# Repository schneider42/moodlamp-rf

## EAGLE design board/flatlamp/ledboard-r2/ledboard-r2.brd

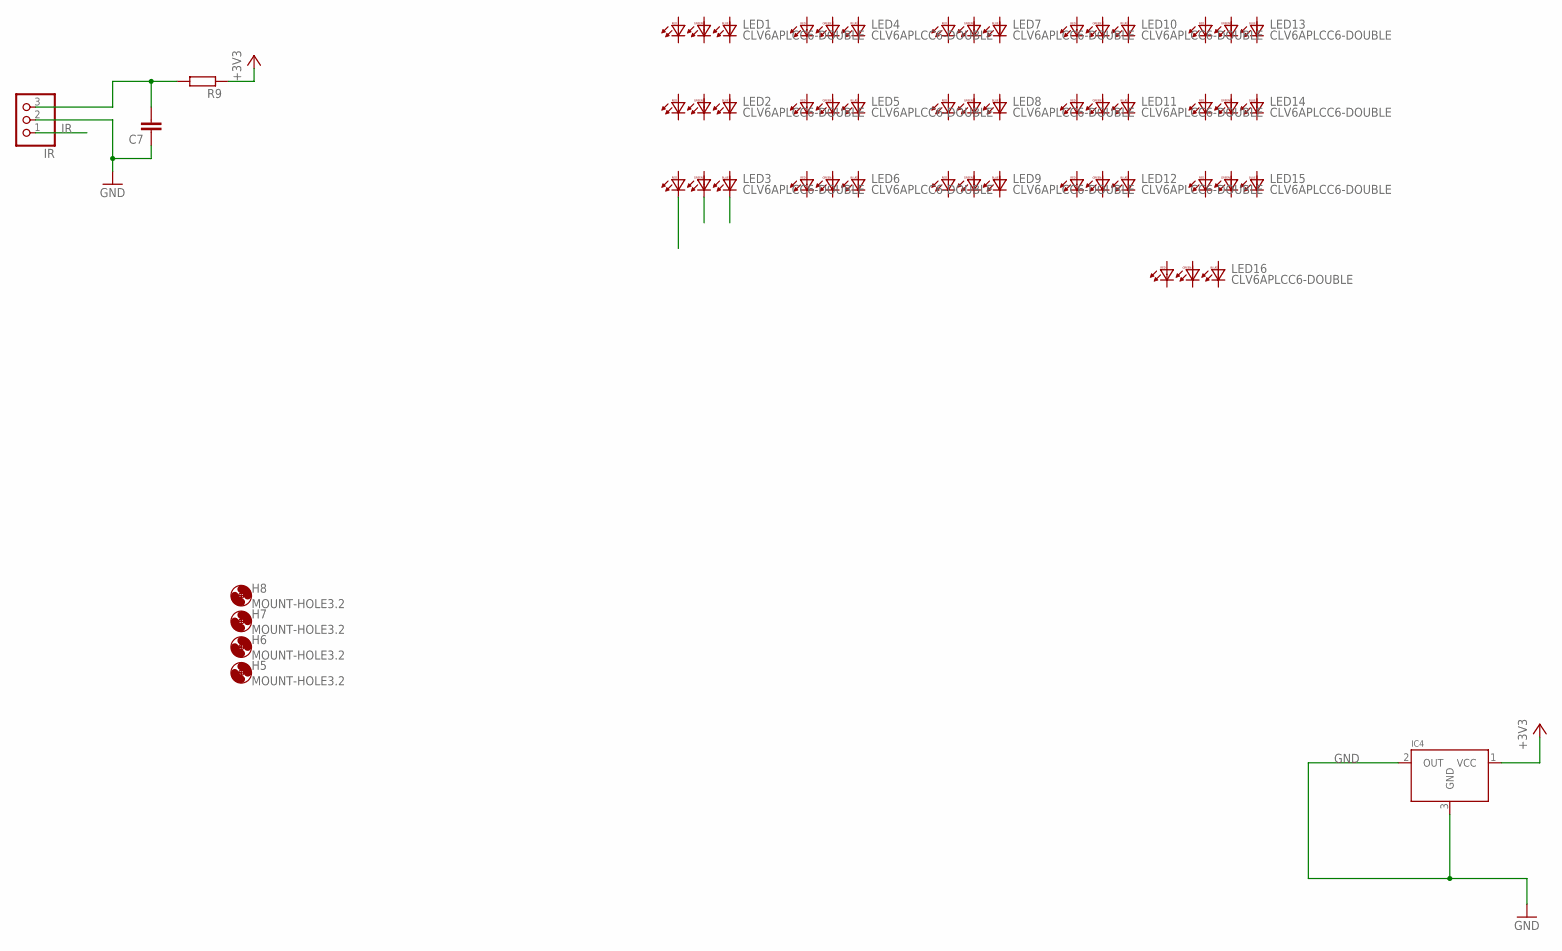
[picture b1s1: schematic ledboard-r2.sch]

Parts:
C7: C-EUC0805; C0805
H5, H6, H7, H8: MOUNT-HOLE3.2; 3,2
IC4: MCP9701T-E/TTCTREFLOW; SOT23-R
IR: PINHD-1X3; 1X03
LED1, LED2, LED3, LED4, LED5, LED6, LED7, LED8, LED9, LED10, LED11, LED12, LED13, LED14, LED15, LED16: CLV6APLCC6-DOUBLE; PLCC6-DOUBLE
R9: R-EU_R0805; R0805

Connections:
+3V3: IC4.1 (VCC), R9.1
GND: C7.1, IC4.2 (OUT), IC4.3 (GND), IR.2
IR: IR.1
unnamed: C7.2, IR.3, R9.2

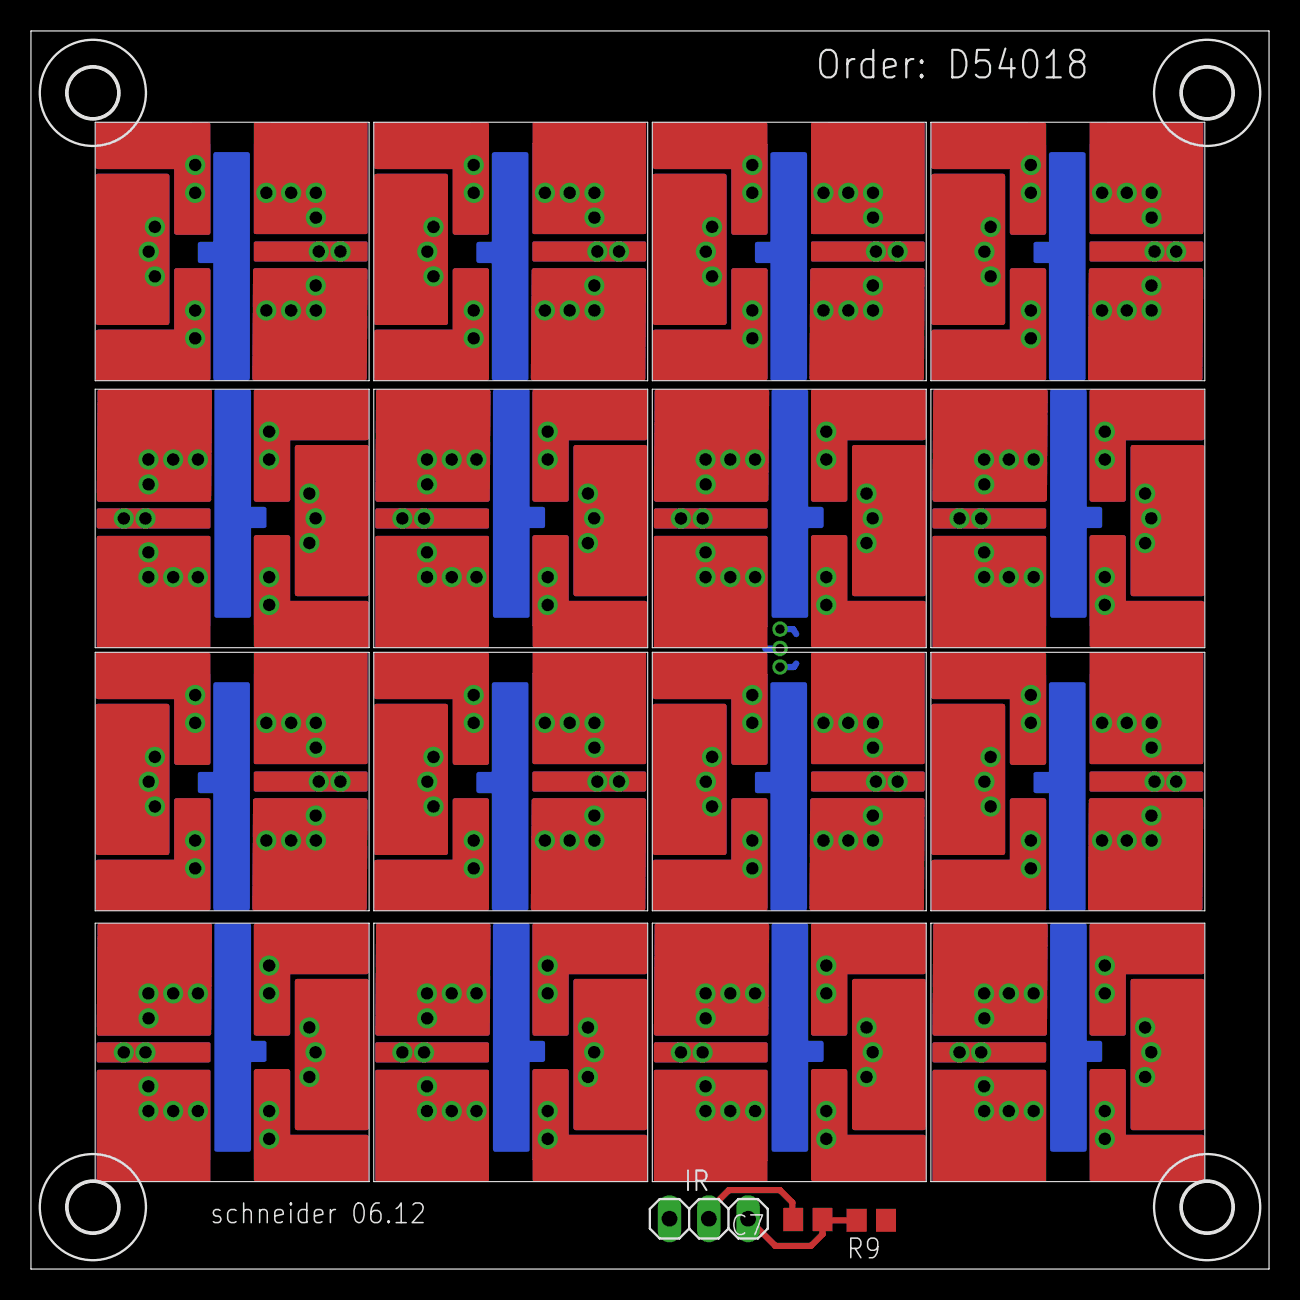
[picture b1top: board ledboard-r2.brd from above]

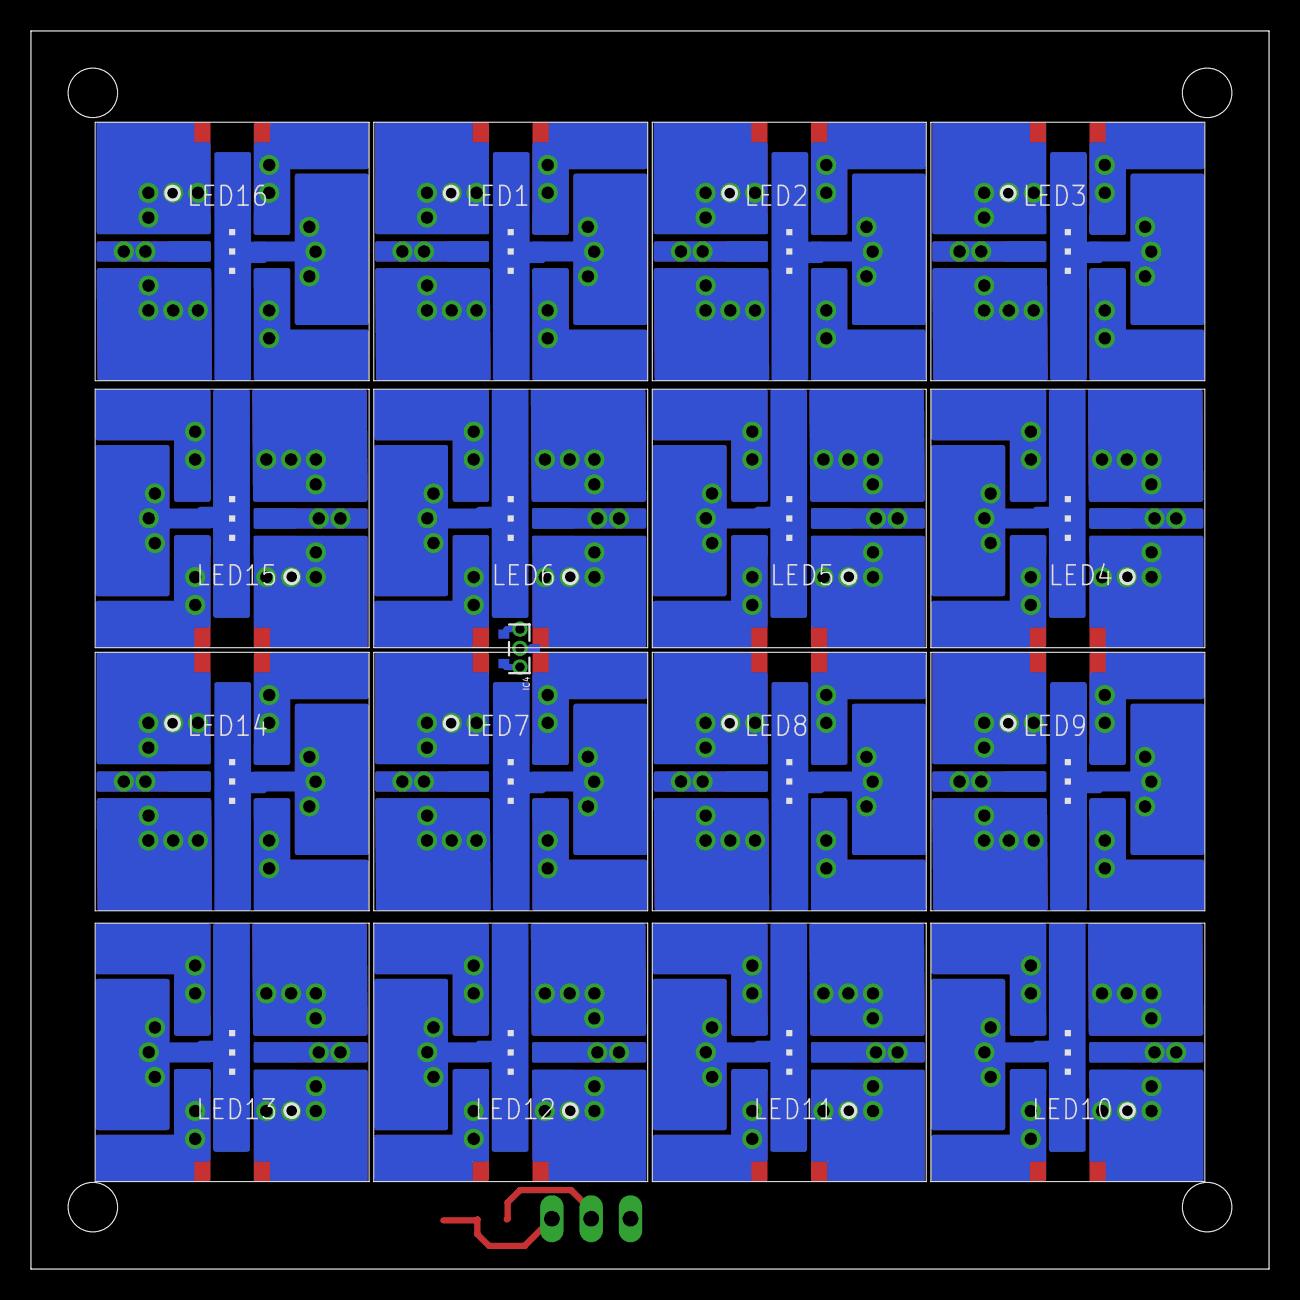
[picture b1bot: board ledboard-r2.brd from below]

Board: 2 copper layers, 80.0 x 80.0 mm, 24 parts (17 on the bottom side), 3 nets.

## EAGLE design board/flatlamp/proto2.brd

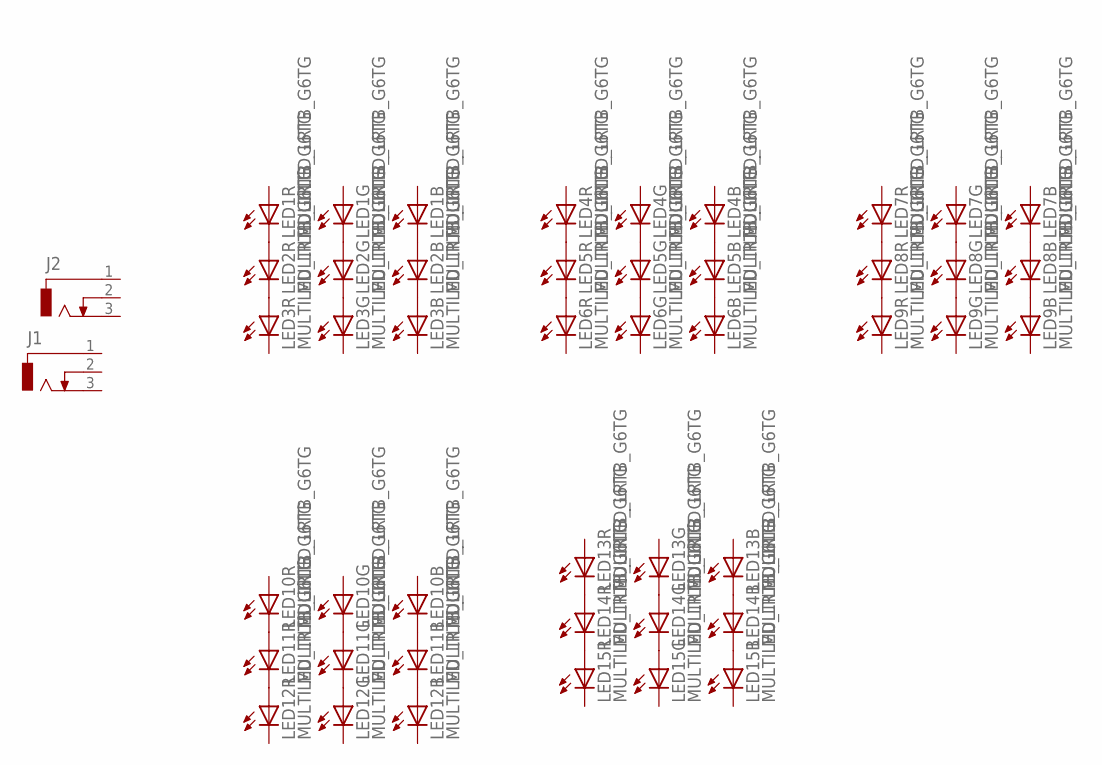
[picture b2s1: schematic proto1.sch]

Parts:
J1, J2: DCJ0303
LED1, LED2, LED3, LED4, LED5, LED6, LED7, LED8, LED9, LED10, LED11, LED12, LED13, LED14, LED15: MULTILED_LRTB_G6TG; P-LCC-6_TOPLED

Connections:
unnamed: LED1.C1 (C), LED2.A1 (A)
unnamed: LED1.C2 (C), LED2.A2 (A)
unnamed: LED1.C3 (C), LED2.A3 (A)
unnamed: LED2.C3 (C), LED3.A3 (A)
unnamed: LED2.C2 (C), LED3.A2 (A)
unnamed: LED2.C1 (C), LED3.A1 (A)
unnamed: LED4.C1 (C), LED5.A1 (A)
unnamed: LED4.C2 (C), LED5.A2 (A)
unnamed: LED4.C3 (C), LED5.A3 (A)
unnamed: LED5.C3 (C), LED6.A3 (A)
unnamed: LED5.C2 (C), LED6.A2 (A)
unnamed: LED5.C1 (C), LED6.A1 (A)
unnamed: LED7.C1 (C), LED8.A1 (A)
unnamed: LED7.C2 (C), LED8.A2 (A)
unnamed: LED7.C3 (C), LED8.A3 (A)
unnamed: LED8.C1 (C), LED9.A1 (A)
unnamed: LED8.C2 (C), LED9.A2 (A)
unnamed: LED8.C3 (C), LED9.A3 (A)
unnamed: LED11.C1 (C), LED12.A1 (A)
unnamed: LED10.C1 (C), LED11.A1 (A)
unnamed: LED10.C2 (C), LED11.A2 (A)
unnamed: LED11.C2 (C), LED12.A2 (A)
unnamed: LED10.C3 (C), LED11.A3 (A)
unnamed: LED11.C3 (C), LED12.A3 (A)
unnamed: LED13.C1 (C), LED14.A1 (A)
unnamed: LED13.C2 (C), LED14.A2 (A)
unnamed: LED13.C3 (C), LED14.A3 (A)
unnamed: LED14.C1 (C), LED15.A1 (A)
unnamed: LED14.C2 (C), LED15.A2 (A)
unnamed: LED14.C3 (C), LED15.A3 (A)

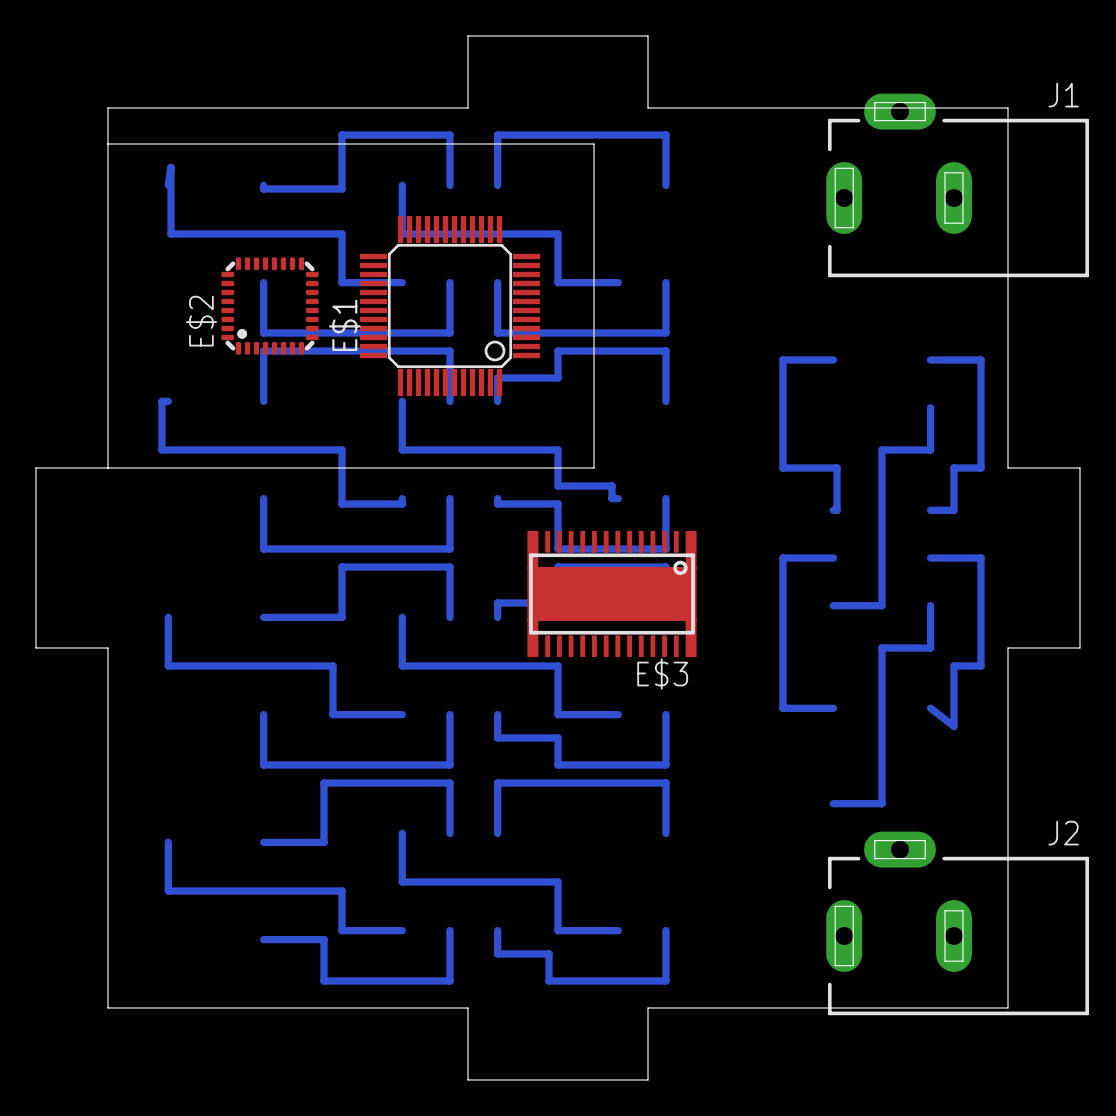
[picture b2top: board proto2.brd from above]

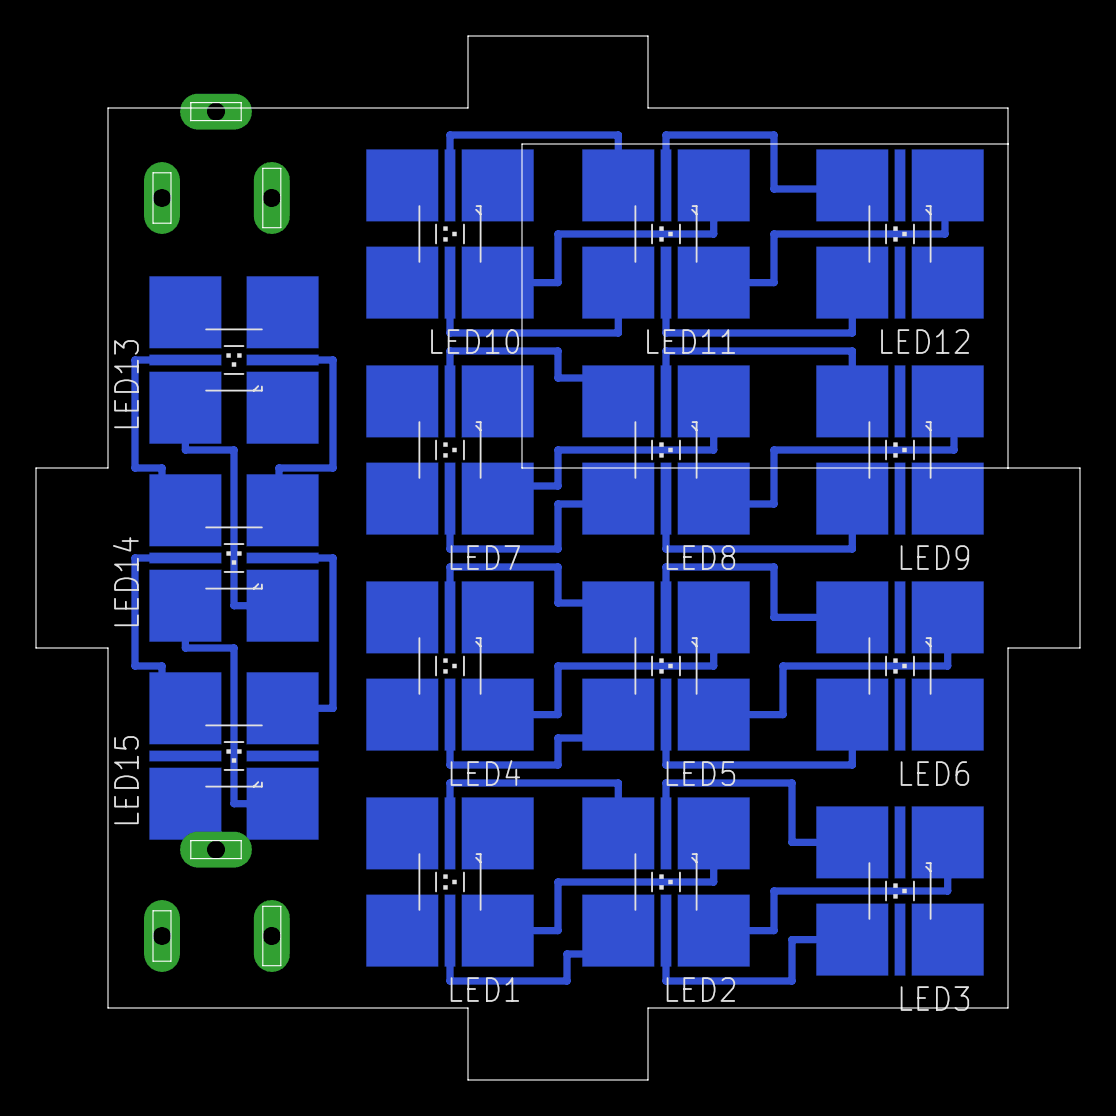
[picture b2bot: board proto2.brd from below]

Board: 2 copper layers, 58.0 x 58.0 mm, 20 parts (15 on the bottom side), 30 nets.

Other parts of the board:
E$1: TQFP48
E$2: MLF32
E$3: HTSSOP28PWP
